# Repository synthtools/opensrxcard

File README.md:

# opensrxcard
opensrxcard is an open source SRX card project that consists of 
- An SRX card that can be used in Roland devices like the Fantom X/XR (other 5V devices like XV5080/XV3080 etc. in the future)
- An Arudino Due based programmer that allows to dump, program and erase SRX cards.

This is work in progress. Keep watching.

# Further information and documentation
Please go to the [wiki for detailed documentation](https://github.com/synthtools/opensrxcard/wiki).

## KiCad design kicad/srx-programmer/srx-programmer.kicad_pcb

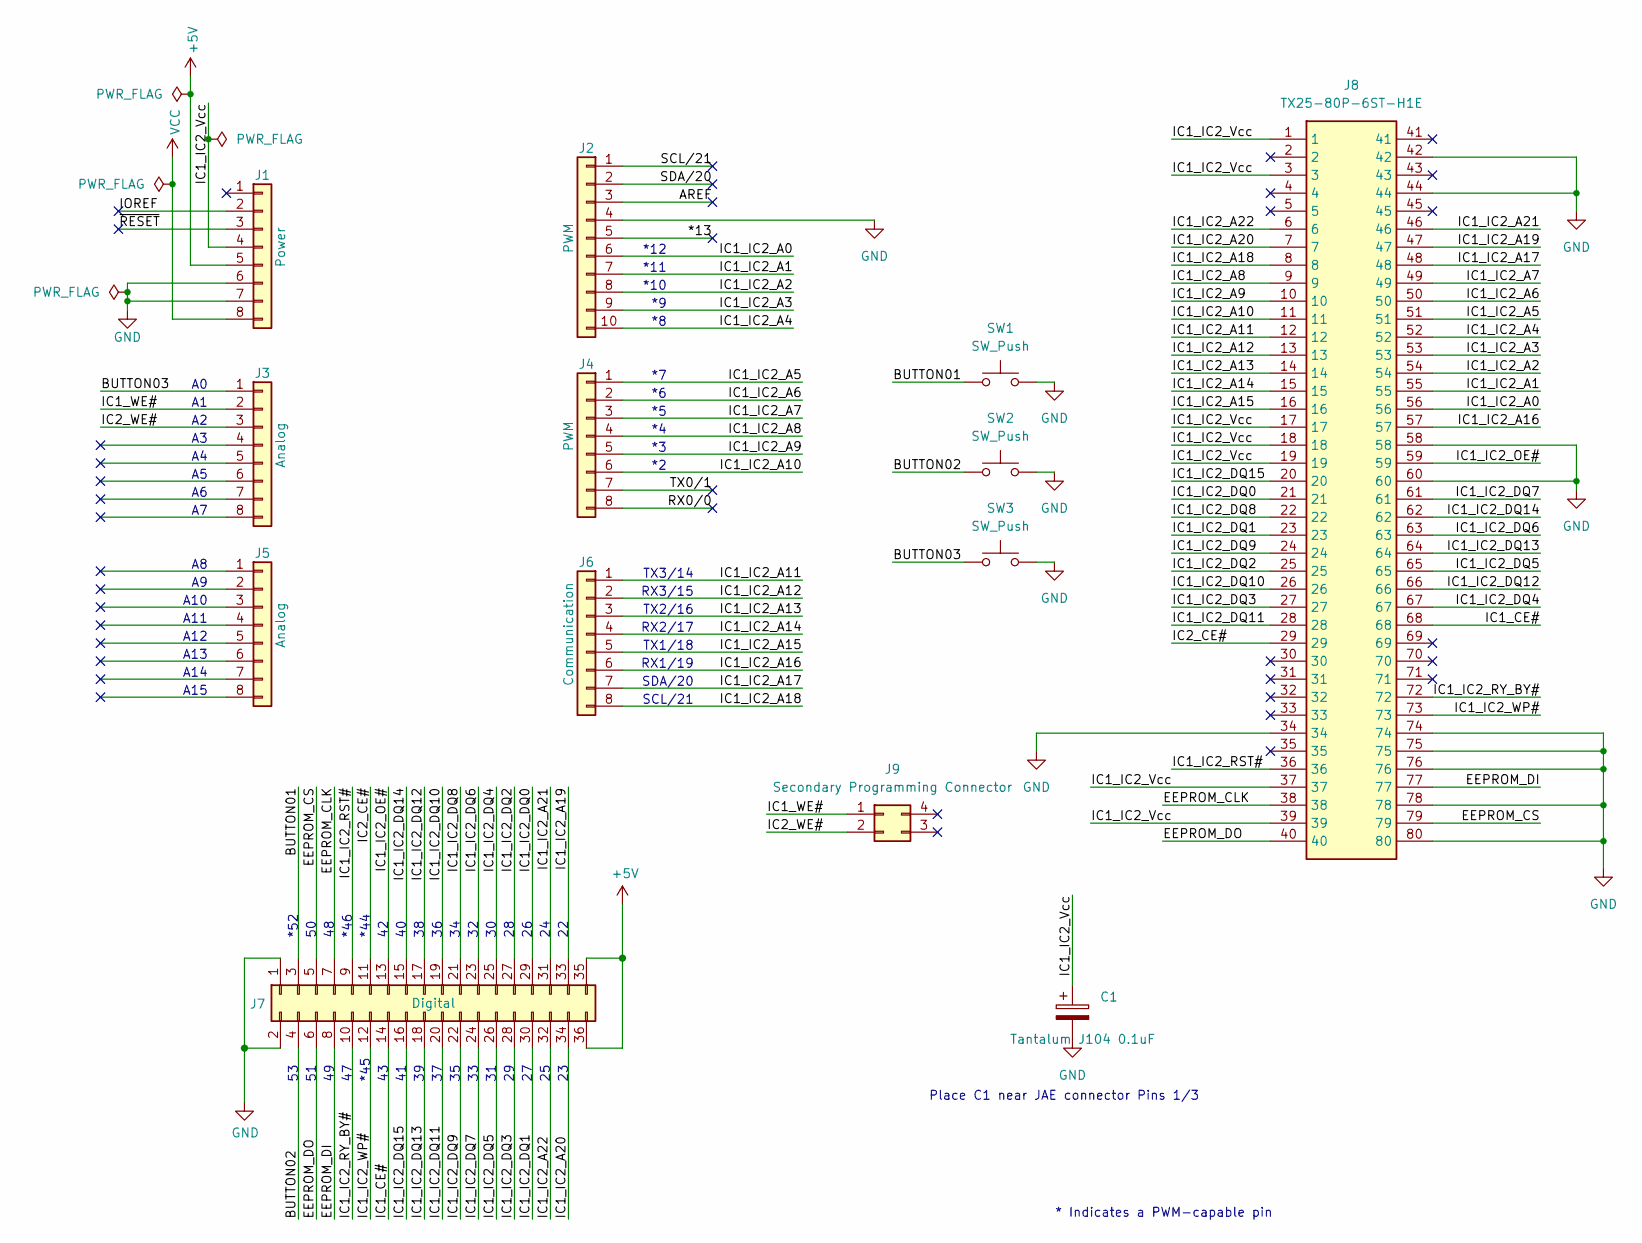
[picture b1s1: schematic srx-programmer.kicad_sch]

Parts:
C1: Tantalum J104 0.1uF; CP_EIA-3216-12_Kemet-S_Pad1.58x1.35mm_HandSolder
J1: Power; PinHeader_1x08_P2.54mm_Vertical
J2: PWM; PinHeader_1x10_P2.54mm_Vertical
J3, J5: Analog; PinHeader_1x08_P2.54mm_Vertical
J4: PWM; PinHeader_1x08_P2.54mm_Vertical
J6: Communication; PinHeader_1x08_P2.54mm_Vertical
J7: Digital; PinHeader_2x18_P2.54mm_Vertical
J8: TX25-80P-6ST-H1E; JAE_TX25-80P-6ST-H1E; Mouser Part Number 656-TX2580P6STH1E
J9: Secondary Programming Connector; PinHeader_2x02_P2.54mm_Vertical
SW1, SW2, SW3: SW_Push; SW_PUSH_6mm

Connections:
+5V: J1.5, J7.35, J7.36
/*13: J2.5
/AREF: J2.3
/BUTTON01: J7.3, SW1.1
/BUTTON02: J7.4, SW2.1
/BUTTON03: J3.1, SW3.1
/EEPROM_CLK: J7.7, J8.38
/EEPROM_CS: J7.5, J8.79
/EEPROM_DI: J7.8, J8.77
/EEPROM_DO: J7.6, J8.40
/IC1_CE#: J7.14, J8.68
/IC1_IC2_A0: J2.6, J8.56
/IC1_IC2_A1: J2.7, J8.55
/IC1_IC2_A2: J2.8, J8.54
/IC1_IC2_A3: J2.9, J8.53
/IC1_IC2_A4: J2.10, J8.52
/IC1_IC2_A5: J4.1, J8.51
/IC1_IC2_A6: J4.2, J8.50
/IC1_IC2_A7: J4.3, J8.49
/IC1_IC2_A8: J4.4, J8.9
/IC1_IC2_A9: J4.5, J8.10
/IC1_IC2_A10: J4.6, J8.11
/IC1_IC2_A11: J6.1, J8.12
/IC1_IC2_A12: J6.2, J8.13
/IC1_IC2_A13: J6.3, J8.14
/IC1_IC2_A14: J6.4, J8.15
/IC1_IC2_A15: J6.5, J8.16
/IC1_IC2_A16: J6.6, J8.57
/IC1_IC2_A17: J6.7, J8.48
/IC1_IC2_A18: J6.8, J8.8
/IC1_IC2_A19: J7.33, J8.47
/IC1_IC2_A20: J7.34, J8.7
/IC1_IC2_A21: J7.31, J8.46
/IC1_IC2_A22: J7.32, J8.6
/IC1_IC2_DQ0: J7.29, J8.21
/IC1_IC2_DQ1: J7.30, J8.23
/IC1_IC2_DQ2: J7.27, J8.25
/IC1_IC2_DQ3: J7.28, J8.27
/IC1_IC2_DQ4: J7.25, J8.67
/IC1_IC2_DQ5: J7.26, J8.65
/IC1_IC2_DQ6: J7.23, J8.63
/IC1_IC2_DQ7: J7.24, J8.61
/IC1_IC2_DQ8: J7.21, J8.22
/IC1_IC2_DQ9: J7.22, J8.24
/IC1_IC2_DQ10: J7.19, J8.26
/IC1_IC2_DQ11: J7.20, J8.28
/IC1_IC2_DQ12: J7.17, J8.66
/IC1_IC2_DQ13: J7.18, J8.64
/IC1_IC2_DQ14: J7.15, J8.62
/IC1_IC2_DQ15: J7.16, J8.20
/IC1_IC2_OE#: J7.13, J8.59
/IC1_IC2_RST#: J7.9, J8.36
/IC1_IC2_RY_BY#: J7.10, J8.72
/IC1_IC2_Vcc: C1.1, J1.4, J8.1, J8.3, J8.17, J8.18, J8.19, J8.37, J8.39
/IC1_IC2_WP#: J7.12, J8.73
/IC1_WE#: J3.2, J9.1
/IC2_CE#: J7.11, J8.29
/IC2_WE#: J3.3, J9.2
/IOREF: J1.2
/RX0/0: J4.8
/SCL/21: J2.1
/SDA/20: J2.2
/TX0/1: J4.7
/~RESET: J1.3
GND: C1.2, J1.6, J1.7, J2.4, J7.1, J7.2, J8.34, J8.42, J8.44, J8.58, J8.60, J8.74, J8.75, J8.76, J8.78, J8.80, SW1.2, SW2.2, SW3.2
VCC: J1.8

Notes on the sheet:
TX1/18
RX2/17
*12
SCL/21
TX2/16
A11
*44
RX3/15
*45
A10
A12
SDA/20
RX1/19
*11
Place C1 near JAE connector Pins 1/3
* Indicates a PWM-capable pin
*46
A15
*10
A14
A13
*52
TX3/14

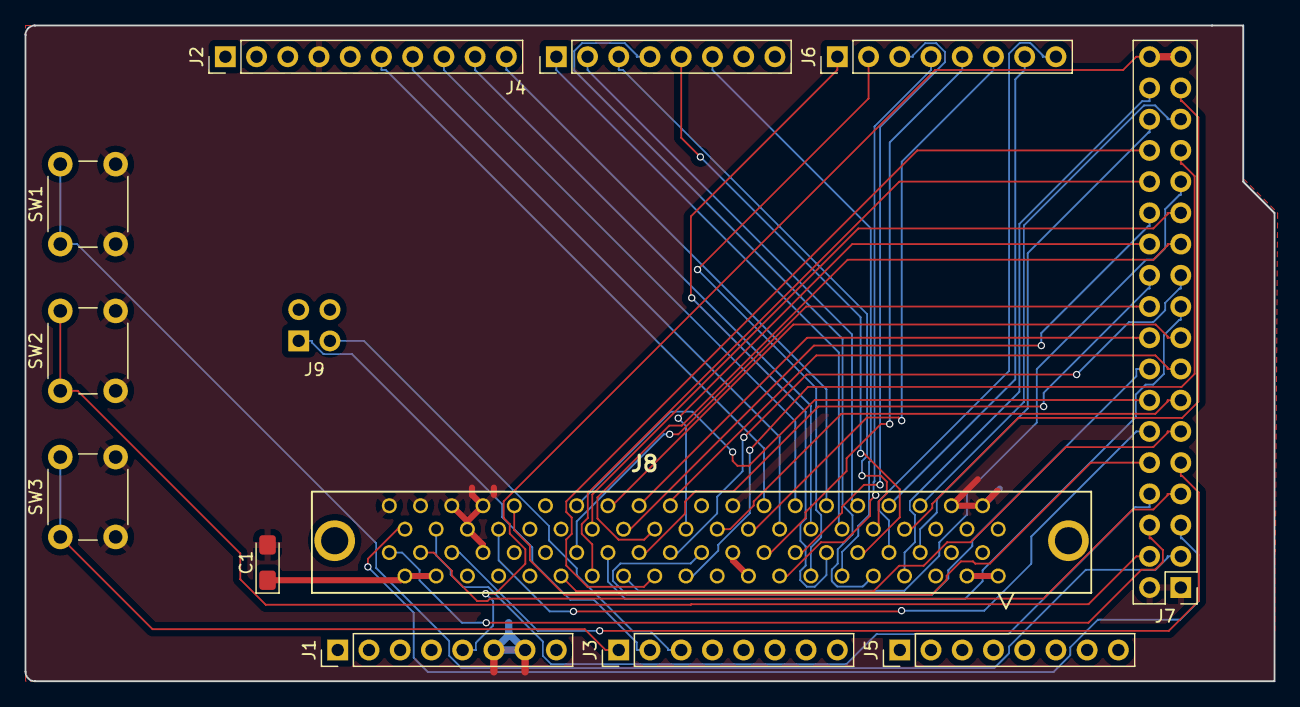
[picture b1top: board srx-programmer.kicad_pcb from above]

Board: 4 copper layers, 101.6 x 53.3 mm, 13 parts (1 on the bottom side), 57 nets.

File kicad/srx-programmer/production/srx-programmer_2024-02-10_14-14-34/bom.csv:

Designator,Footprint,Quantity,Value,LCSC Part #
C1,CP_EIA-3216-12_Kemet-S_Pad1.58x1.35mm_HandSolder,1,Tantalum J104 0.1uF,
J1,PinHeader_1x08_P2.54mm_Vertical,1,Power,
J2,PinHeader_1x10_P2.54mm_Vertical,1,PWM,
"J3, J5",PinHeader_1x08_P2.54mm_Vertical,2,Analog,
J4,PinHeader_1x08_P2.54mm_Vertical,1,PWM,
J6,PinHeader_1x08_P2.54mm_Vertical,1,Communication,
J7,PinHeader_2x18_P2.54mm_Vertical,1,Digital,
J8,JAE_TX25-80P-6ST-H1E,1,TX25-80P-6ST-H1E,
J9,PinHeader_2x02_P2.54mm_Vertical,1,Secondary Programming Connector,
"SW1, SW2, SW3",SW_PUSH_6mm,3,SW_Push,

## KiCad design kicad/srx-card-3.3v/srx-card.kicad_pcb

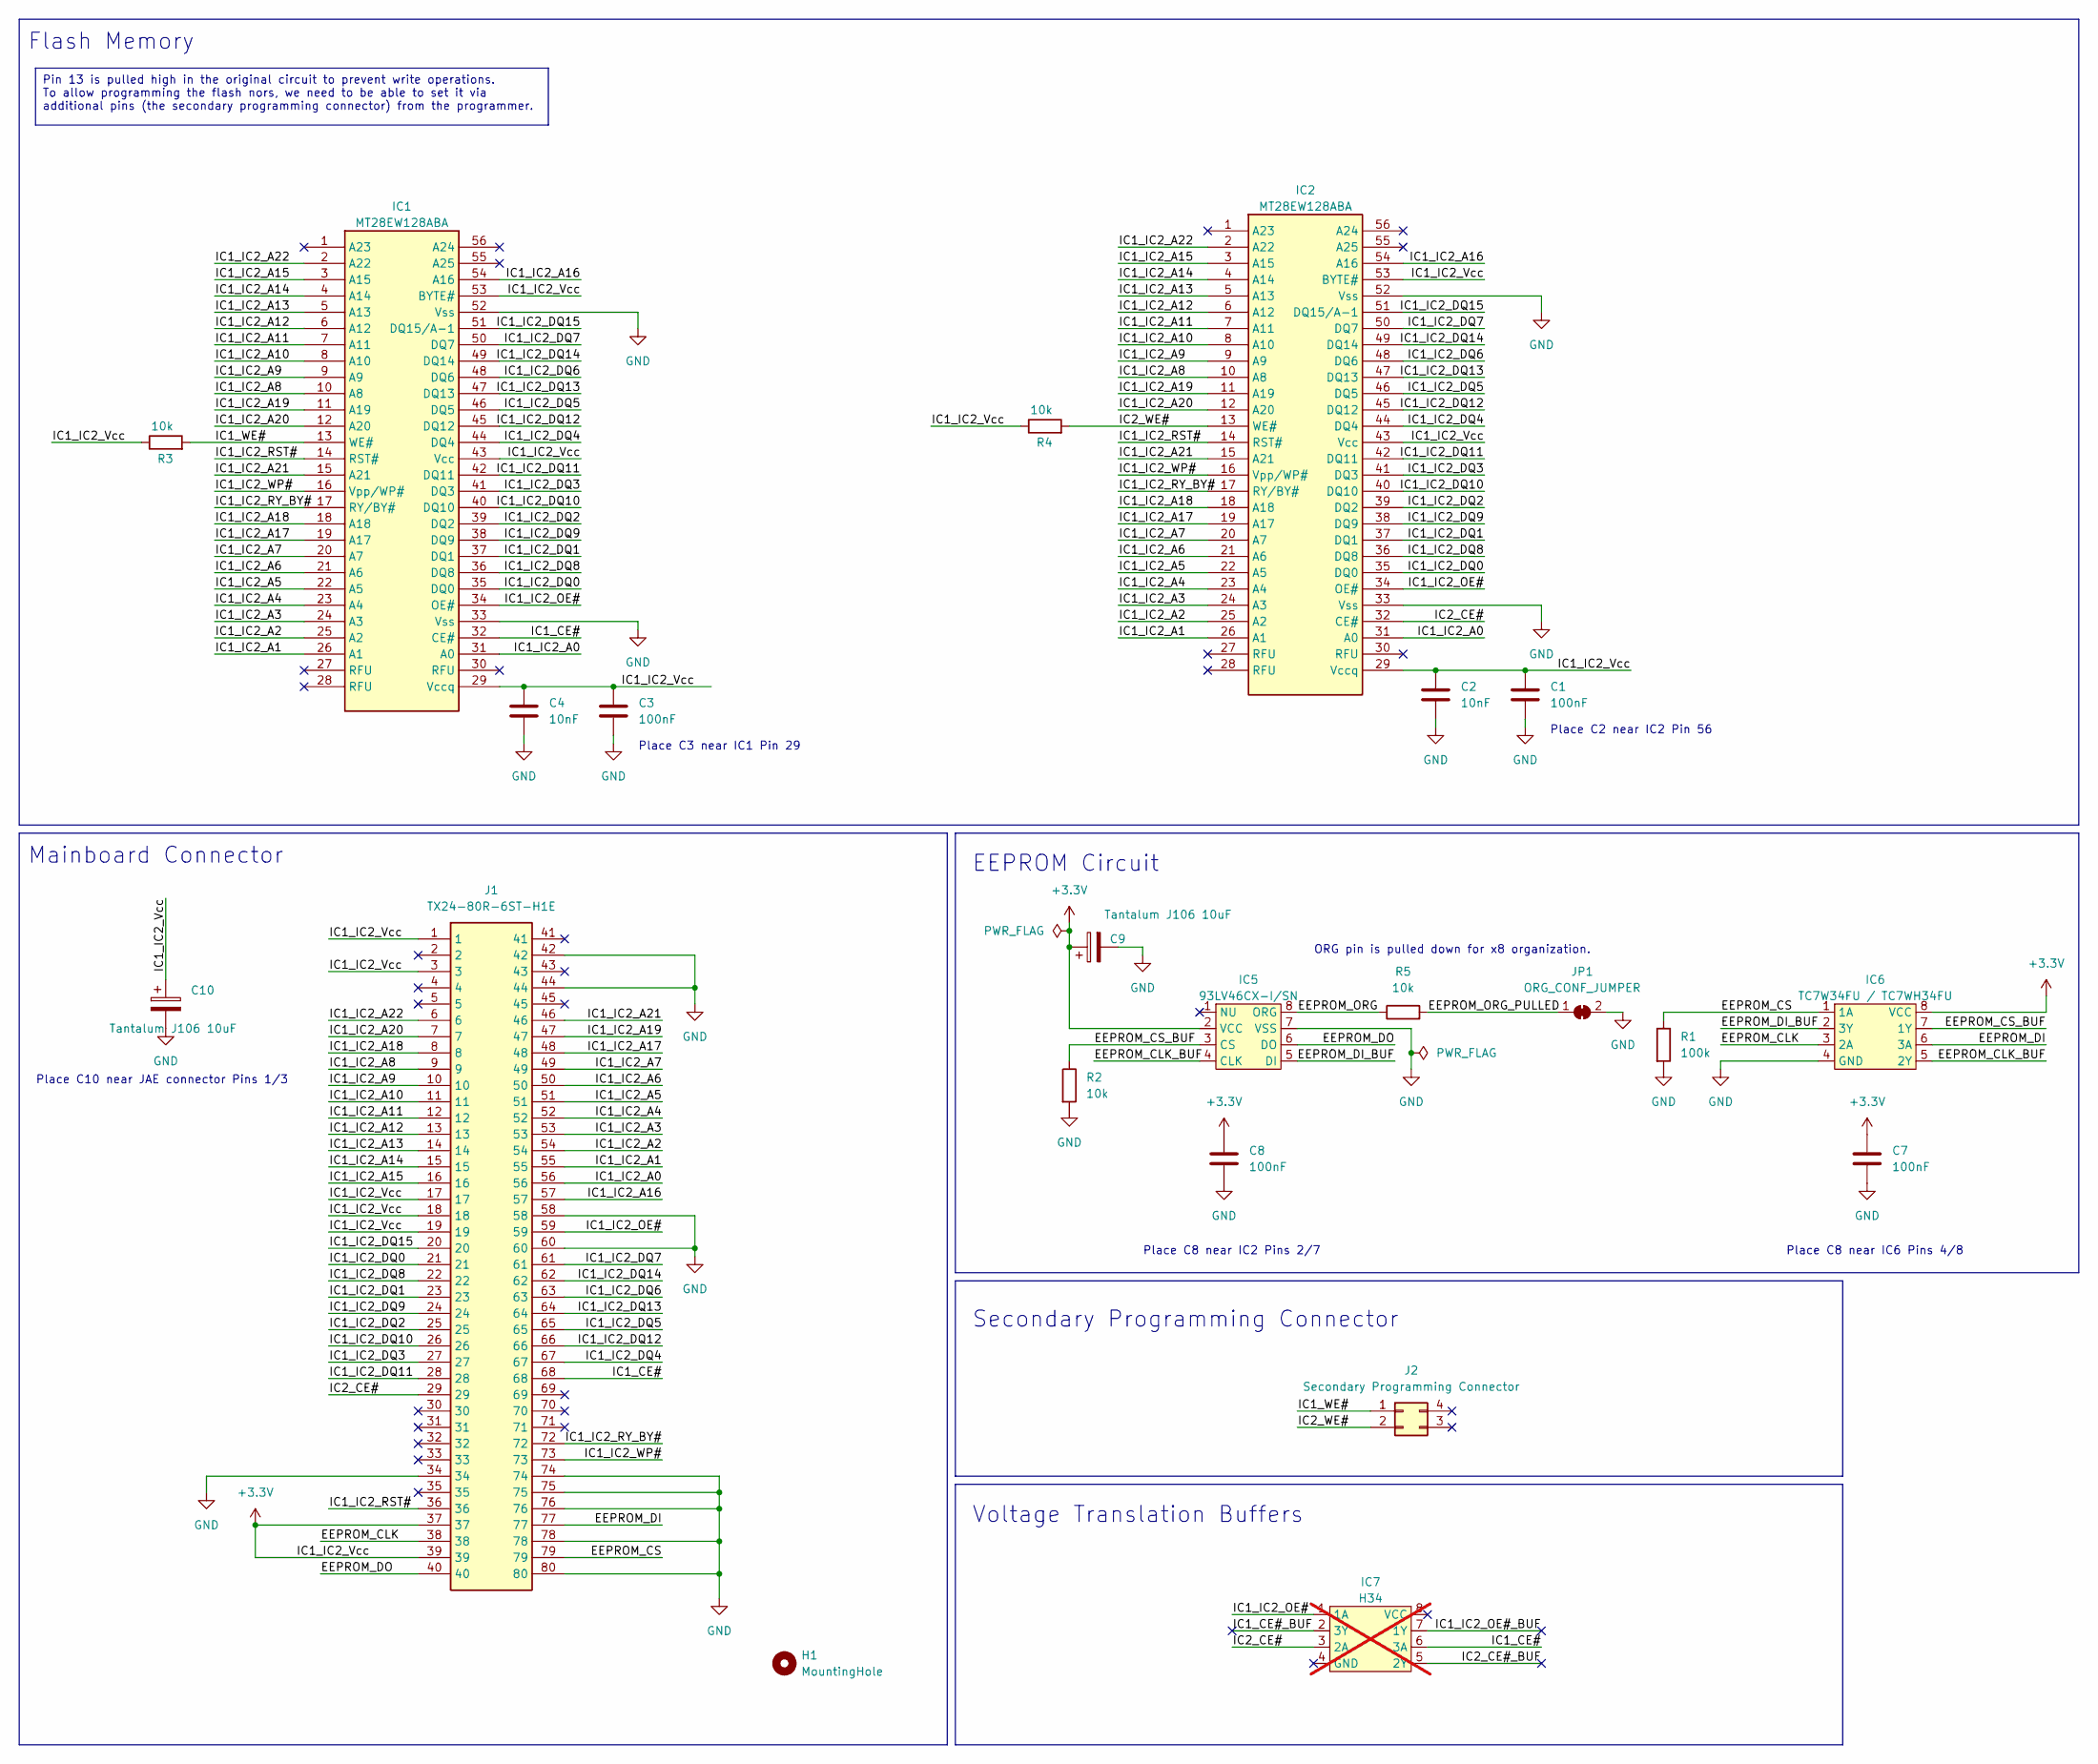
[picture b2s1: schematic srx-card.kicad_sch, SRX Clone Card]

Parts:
C1, C3, C7, C8: 100nF; C_0805_2012Metric_Pad1.18x1.45mm_HandSolder; LCSC C710699
C2, C4: 10nF; C_0805_2012Metric_Pad1.18x1.45mm_HandSolder; LCSC C161252
C9, C10: Tantalum J106 10uF; CP_EIA-3528-21_Kemet-B_Pad1.50x2.35mm_HandSolder; LCSC C110050
H1: MountingHole; MountingHole_5mm
IC1, IC2: MT28EW128ABA; TSOP-I-56_18.4x14mm_P0.5mm; LCSC C598856
IC5: 93LV46CX-I/SN; SOIC-8_3.9x4.9mm_P1.27mm
IC6: TC7W34FU / TC7WH34FU; SSOP-8_2.95x2.8mm_P0.65mm; LCSC C2676253
IC7: H34; SSOP-8_2.95x2.8mm_P0.65mm; not fitted
J1: TX24-80R-6ST-H1E; JAE_TX24-80R-6ST-H1E; Mouser Part Number 656-TX24-80R-6ST-H1E
J2: Secondary Programming Connector; PinHeader_2x02_P2.54mm_Vertical
JP1: ORG_CONF_JUMPER; SolderJumper-2_P1.3mm_Bridged_Pad1.0x1.5mm
R1: 100k; R_0805_2012Metric_Pad1.20x1.40mm_HandSolder; LCSC C122537
R2, R3, R4, R5: 10k; R_0805_2012Metric_Pad1.20x1.40mm_HandSolder; LCSC C441955

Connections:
+3.3V: C1.1, C2.1, C3.1, C4.1, C7.1, C8.1, C9.1, C10.1, IC1.29 (Vccq), IC1.43 (Vcc), IC1.53 (BYTE#), IC2.29 (Vccq), IC2.43 (Vcc), IC2.53 (BYTE#), IC5.2 (VCC), IC6.8 (VCC), J1.1, J1.3, J1.17, J1.18, J1.19, J1.37, J1.39, R3.1, R4.1
/EEPROM_CLK: IC6.3 (2A), J1.38
/EEPROM_CLK_BUF: IC5.4 (CLK), IC6.5 (2Y)
/EEPROM_CS: IC6.1 (1A), J1.79, R1.1
/EEPROM_CS_BUF: IC5.3 (CS), IC6.7 (1Y), R2.1
/EEPROM_DI: IC6.6 (3A), J1.77
/EEPROM_DI_BUF: IC5.5 (DI), IC6.2 (3Y)
/EEPROM_DO: IC5.6 (DO), J1.40
/EEPROM_ORG: IC5.8 (ORG), R5.1
/EEPROM_ORG_PULLED: JP1.1 (A), R5.2
/IC1_CE#: IC1.32 (CE#), IC7.6 (3A), J1.68
/IC1_IC2_A0: IC1.31 (A0), IC2.31 (A0), J1.56
/IC1_IC2_A1: IC1.26 (A1), IC2.26 (A1), J1.55
/IC1_IC2_A2: IC1.25 (A2), IC2.25 (A2), J1.54
/IC1_IC2_A3: IC1.24 (A3), IC2.24 (A3), J1.53
/IC1_IC2_A4: IC1.23 (A4), IC2.23 (A4), J1.52
/IC1_IC2_A5: IC1.22 (A5), IC2.22 (A5), J1.51
/IC1_IC2_A6: IC1.21 (A6), IC2.21 (A6), J1.50
/IC1_IC2_A7: IC1.20 (A7), IC2.20 (A7), J1.49
/IC1_IC2_A8: IC1.10 (A8), IC2.10 (A8), J1.9
/IC1_IC2_A9: IC1.9 (A9), IC2.9 (A9), J1.10
/IC1_IC2_A10: IC1.8 (A10), IC2.8 (A10), J1.11
/IC1_IC2_A11: IC1.7 (A11), IC2.7 (A11), J1.12
/IC1_IC2_A12: IC1.6 (A12), IC2.6 (A12), J1.13
/IC1_IC2_A13: IC1.5 (A13), IC2.5 (A13), J1.14
/IC1_IC2_A14: IC1.4 (A14), IC2.4 (A14), J1.15
/IC1_IC2_A15: IC1.3 (A15), IC2.3 (A15), J1.16
/IC1_IC2_A16: IC1.54 (A16), IC2.54 (A16), J1.57
/IC1_IC2_A17: IC1.19 (A17), IC2.19 (A17), J1.48
/IC1_IC2_A18: IC1.18 (A18), IC2.18 (A18), J1.8
/IC1_IC2_A19: IC1.11 (A19), IC2.11 (A19), J1.47
/IC1_IC2_A20: IC1.12 (A20), IC2.12 (A20), J1.7
/IC1_IC2_A21: IC1.15 (A21), IC2.15 (A21), J1.46
/IC1_IC2_A22: IC1.2 (A22), IC2.2 (A22), J1.6
/IC1_IC2_DQ0: IC1.35 (DQ0), IC2.35 (DQ0), J1.21
/IC1_IC2_DQ1: IC1.37 (DQ1), IC2.37 (DQ1), J1.23
/IC1_IC2_DQ2: IC1.39 (DQ2), IC2.39 (DQ2), J1.25
/IC1_IC2_DQ3: IC1.41 (DQ3), IC2.41 (DQ3), J1.27
/IC1_IC2_DQ4: IC1.44 (DQ4), IC2.44 (DQ4), J1.67
/IC1_IC2_DQ5: IC1.46 (DQ5), IC2.46 (DQ5), J1.65
/IC1_IC2_DQ6: IC1.48 (DQ6), IC2.48 (DQ6), J1.63
/IC1_IC2_DQ7: IC1.50 (DQ7), IC2.50 (DQ7), J1.61
/IC1_IC2_DQ8: IC1.36 (DQ8), IC2.36 (DQ8), J1.22
/IC1_IC2_DQ9: IC1.38 (DQ9), IC2.38 (DQ9), J1.24
/IC1_IC2_DQ10: IC1.40 (DQ10), IC2.40 (DQ10), J1.26
/IC1_IC2_DQ11: IC1.42 (DQ11), IC2.42 (DQ11), J1.28
/IC1_IC2_DQ12: IC1.45 (DQ12), IC2.45 (DQ12), J1.66
/IC1_IC2_DQ13: IC1.47 (DQ13), IC2.47 (DQ13), J1.64
/IC1_IC2_DQ14: IC1.49 (DQ14), IC2.49 (DQ14), J1.62
/IC1_IC2_DQ15: IC1.51 (DQ15/A-1), IC2.51 (DQ15/A-1), J1.20
/IC1_IC2_OE#: IC1.34 (OE#), IC2.34 (OE#), IC7.1 (1A), J1.59
/IC1_IC2_RST#: IC1.14 (RST#), IC2.14 (RST#), J1.36
/IC1_IC2_RY_BY#: IC1.17 (RY/BY#), IC2.17 (RY/BY#), J1.72
/IC1_IC2_WP#: IC1.16 (Vpp/WP#), IC2.16 (Vpp/WP#), J1.73
/IC1_WE#: IC1.13 (WE#), J2.1, R3.2
/IC2_CE#: IC2.32 (CE#), IC7.3 (2A), J1.29
/IC2_WE#: IC2.13 (WE#), J2.2, R4.2
GND: C1.2, C2.2, C3.2, C4.2, C7.2, C8.2, C9.2, C10.2, IC1.33 (Vss), IC1.52 (Vss), IC2.33 (Vss), IC2.52 (Vss), IC5.7 (VSS), IC6.4 (GND), J1.34, J1.42, J1.44, J1.58, J1.60, J1.74, J1.75, J1.76, J1.78, J1.80, JP1.2 (B), R1.2, R2.2

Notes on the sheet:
Pin 13 is pulled high in the original circuit to prevent write operations. To allow programming the flash nors, we need to be able to set it via additional pins (the secondary programming connector) from the programmer.
Flash Memory
Place C3 near IC1 Pin 29
Place C10 near JAE connector Pins 1/3
Place C2 near IC2 Pin 56
ORG pin is pulled down for x8 organization.
Voltage Translation Buffers
EEPROM Circuit
Place C8 near IC6 Pins 4/8
Place C8 near IC2 Pins 2/7
Secondary Programming Connector
Mainboard Connector

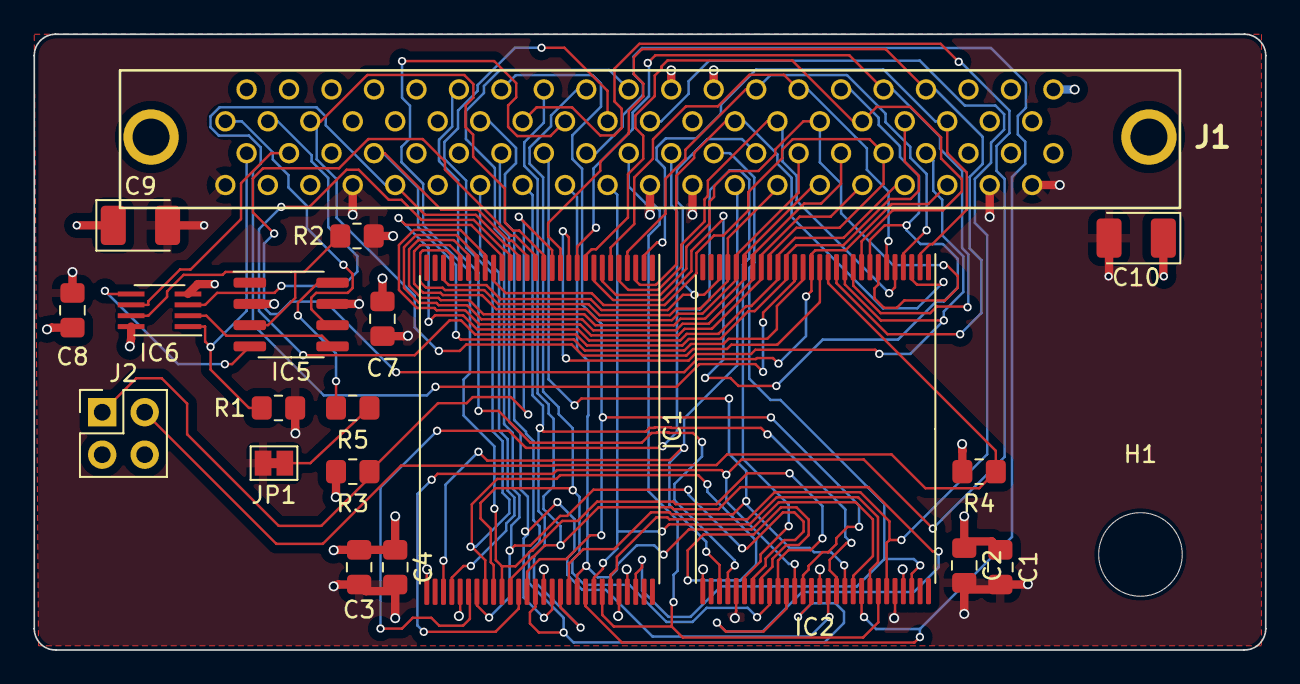
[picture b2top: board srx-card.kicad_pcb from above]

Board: 4 copper layers, 73.7 x 36.8 mm, 21 parts (0 on the bottom side), 58 nets.

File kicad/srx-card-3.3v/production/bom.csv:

Designator,Footprint,Quantity,Value,LCSC Part #
"C1, C3, C7, C8",0805,4,100nF,C710699
C10,CP_EIA-3528-21_Kemet-B_Pad1.50x2.35mm_HandSolder,1,Tantalum J106 10uF,C110050
"C2, C4",0805,2,10nF,C161252
C9,CP_EIA-3528-21_Kemet-B_Pad1.50x2.35mm_HandSolder,1,Tantalum J106 10uF, C110050
"IC1, IC2",TSOP-I-56_18.4x14mm_P0.5mm,2,MT28EW128ABA,C598856
R1,0805,1,100k,C122537
"R2, R3, R4, R5",0805,4,10k,C441955

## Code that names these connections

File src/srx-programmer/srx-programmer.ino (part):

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#define FLASH_RST_n 47
#define FLASH_RY_BY 46
/*
#define EEPROM_CLK 49
#define EEPROM_DI 48
#define EEPROM_CS 51
#define EEPROM_DO 50
*/
#define BUTTON01 53
#define BUTTON02 52
#define BUTTON03 A0
#define IC1_WE_n A1
#define IC2_WE_n A2

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  pinMode(FLASH_DQ12, INPUT);pinMode(FLASH_DQ13, INPUT);pinMode(FLASH_DQ14, INPUT);
  pinMode(FLASH_DQ15, INPUT);
*/
  pinMode(BUTTON01, INPUT_PULLUP);
  pinMode(BUTTON02, INPUT_PULLUP);
  pinMode(BUTTON03, INPUT_PULLUP);

  pinMode(FLASH_OE_n, OUTPUT);
  pinMode(FLASH_IC1_CE_n, OUTPUT);
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  pinMode(FLASH_RST_n, OUTPUT);
  pinMode(FLASH_RY_BY, INPUT);
  /*
  pinMode(EEPROM_CLK, OUTPUT);
  pinMode(EEPROM_DI, INPUT);
  pinMode(EEPROM_CS, OUTPUT);
  pinMode(EEPROM_DO, OUTPUT);
*/
  pinMode(IC1_WE_n, OUTPUT);
  pinMode(IC2_WE_n, OUTPUT);
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
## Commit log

2024-03-05 test
2024-03-19 Fixed a problem when programming images. Should work a lot more stable now.
2024-03-22 robustness fixes.
2024-03-23 Enhanced programming robustness and drastically quicker programming speeds with buffered programming. This should rarely fail now.
